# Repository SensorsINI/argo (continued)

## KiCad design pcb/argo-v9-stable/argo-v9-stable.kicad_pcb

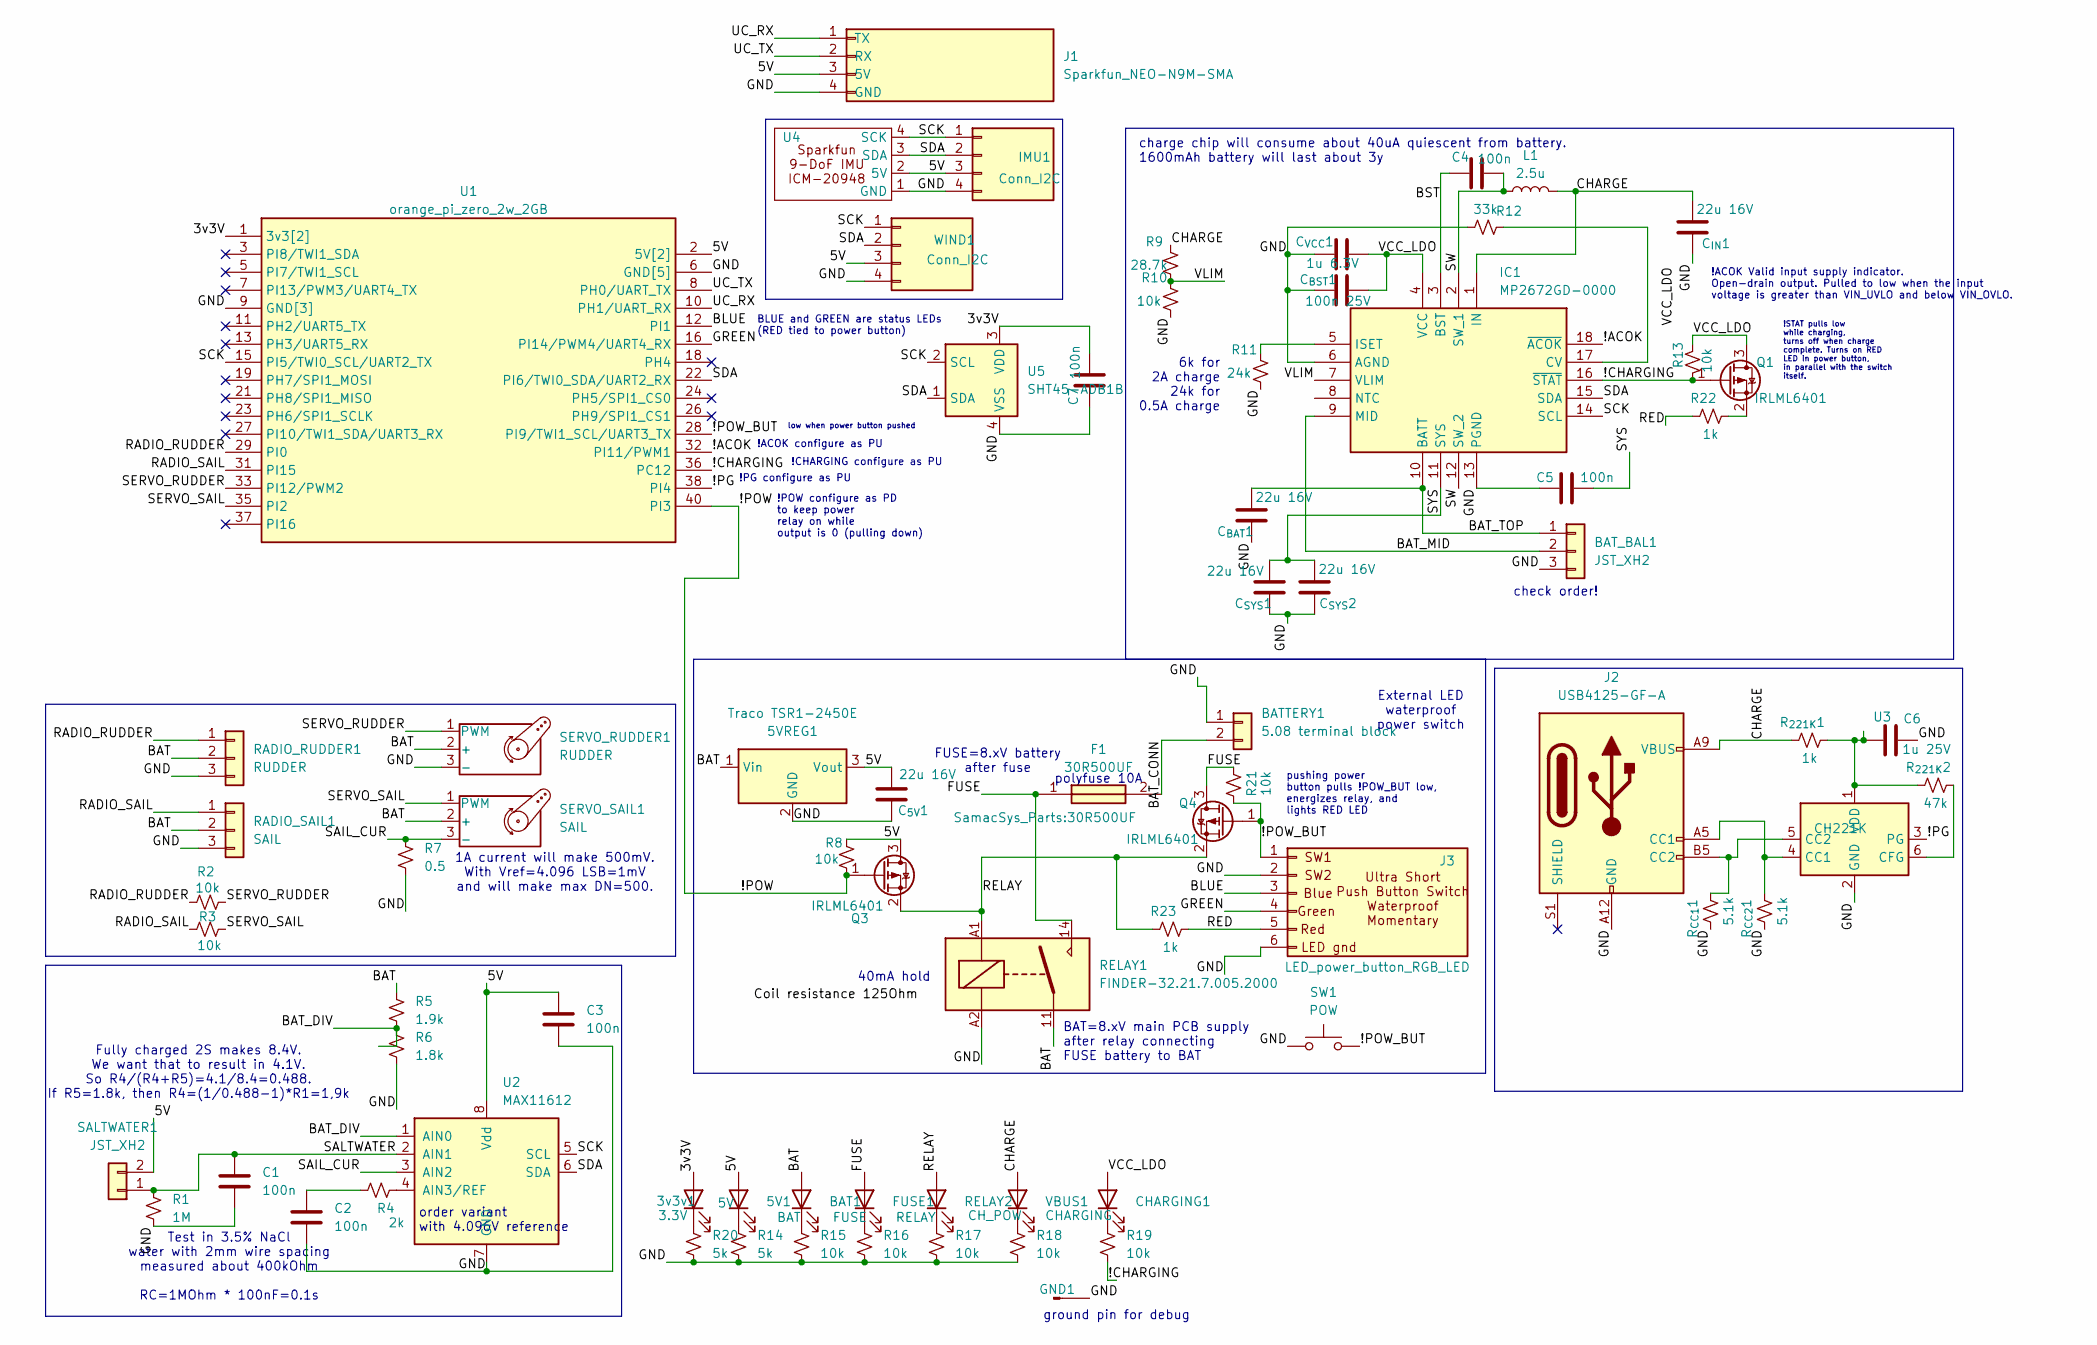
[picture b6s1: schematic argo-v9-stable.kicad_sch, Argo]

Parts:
3v3v1: 3.3V; LED_0603_1608Metric_Pad1.05x0.95mm_HandSolder
5V1: 5V; LED_0603_1608Metric_Pad1.05x0.95mm_HandSolder
5VREG1: Traco TSR1-2450E; Converter_DCDC_TRACO_TSR1-xxxxE_THT
BAT1: BAT; LED_0603_1608Metric_Pad1.05x0.95mm_HandSolder
BATTERY1: 5.08 terminal block; TerminalBlock_Phoenix_MKDS-1,5-2-5.08_1x02_P5.08mm_Horizont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
BAT_BAL1: JST_XH2; JST_XH_S3B-XH-A-1_1x03_P2.50mm_Horizontal
C1, C2, C3, C4, C5, C7: 100n; C_0603_1608Metric_Pad1.08x0.95mm_HandSolder
C6: 1u 25V; C_0603_1608Metric_Pad1.08x0.95mm_HandSolder
CHARGING1: CHARGING; LED_0603_1608Metric_Pad1.05x0.95mm_HandSolder
C_{5V}1: 22u 16V; C_1210_3225Metric_Pad1.33x2.70mm_HandSolder
C_{BAT}1: 22u 16V; C_1210_3225Metric_Pad1.33x2.70mm_HandSolder
C_{BST}1: 100n 25V; C_0603_1608Metric_Pad1.08x0.95mm_HandSolder
C_{IN}1: 22u 16V; C_1210_3225Metric_Pad1.33x2.70mm_HandSolder
C_{SYS}1, C_{SYS}2: 22u 16V; C_1210_3225Metric_Pad1.33x2.70mm_HandSolder
C_{VCC}1: 1u 6.3V; C_0603_1608Metric_Pad1.08x0.95mm_HandSolder
F1: 30R500UF; Mouser Part Number 576-30R500UF
FUSE1: FUSE; LED_0603_1608Metric_Pad1.05x0.95mm_HandSolder
GND1: Conn_01x01_Pin; Pin_D1.0mm_L10.0mm_LooseFit
IC1: MP2672GD-0000; QFN40P200X300X100-18N-D-handsolder; Manufacturer_Part_Number MP2672GD-0000
IMU1: Conn_I2C; JST_XH_B4B-XH-AM_1x04_P2.50mm_Vertical
J1: Sparkfun_NEO-N9M-SMA; Sparkfun_NEO-M9N-SMA-scaled
J2: USB4125-GF-A; USB_C_Receptacle_GCT_USB4125-xx-x-0190_6P_TopMnt_Horizontal
J3: LED_power_button_RGB_LED; JST_XH_B6B-XH-AM_1x06_P2.50mm_Vertical
L1: 2.5u; L_1210_3225Metric_Pad1.42x2.65mm_HandSolder
Q1, Q3, Q4: IRLML6401; SOT-23
R1: 1M; R_0603_1608Metric_Pad0.98x0.95mm_HandSolder
R2, R3, R8, R10, R13, R15, R16, R17, R18, R19, R21: 10k; R_0603_1608Metric_Pad0.98x0.95mm_HandSolder
R4: 2k; R_0603_1608Metric_Pad0.98x0.95mm_HandSolder
R5: 1.9k; R_0603_1608Metric_Pad0.98x0.95mm_HandSolder
R6: 1.8k; R_0603_1608Metric_Pad0.98x0.95mm_HandSolder
R7: 0.5; R_0603_1608Metric_Pad0.98x0.95mm_HandSolder
R9: 28.7k; R_0603_1608Metric_Pad0.98x0.95mm_HandSolder
R11: 24k; R_0603_1608Metric_Pad0.98x0.95mm_HandSolder
R12: 33k; R_0603_1608Metric_Pad0.98x0.95mm_HandSolder
R14, R20: 5k; R_0603_1608Metric_Pad0.98x0.95mm_HandSolder
R22, R23: 1k; R_0603_1608Metric_Pad0.98x0.95mm_HandSolder
RADIO_RUDDER1: RUDDER; PinHeader_1x03_P2.54mm_Vertical
RADIO_SAIL1: SAIL; PinHeader_1x03_P2.54mm_Vertical
RELAY1: FINDER-32.21.7.005.2000; Relay_SPST_Finder_32.21-x300
RELAY2: RELAY; LED_0603_1608Metric_Pad1.05x0.95mm_HandSolder
R_{221K}1: 1k; R_0603_1608Metric_Pad0.98x0.95mm_HandSolder
R_{221K}2: 47k; R_0603_1608Metric_Pad0.98x0.95mm_HandSolder
R_{CC1}1, R_{CC2}1: 5.1k; R_0603_1608Metric_Pad0.98x0.95mm_HandSolder
SALTWATER1: JST_XH2; JST_XH_S2B-XH-A_1x02_P2.50mm_Horizontal
SERVO_RUDDER1: RUDDER; PinHeader_1x03_P2.54mm_Vertical
SERVO_SAIL1: SAIL; PinHeader_1x03_P2.54mm_Vertical
SW1: POW; SW_Tactile_SPST_NO_Straight_CK_PTS636Sx25SMTRLFS
U1: orange_pi_zero_2w_2GB; orange_pi_zero_2w
U2: MAX11612; MSOP-8_3x3mm_P0.65mm
U3: CH221K; TSOT-23-6_HandSoldering
U4: Sparkfun_IMU_ICM-20948
U5: SHT45-ADB1B; Sensirion_DFN-4_1.5x1.5mm_P0.8mm_SHT4x_NoCentralPad
VBUS1: CH_POW; LED_0603_1608Metric_Pad1.05x0.95mm_HandSolder
WIND1: Conn_I2C; JST_XH_B4B-XH-AM_1x04_P2.50mm_Vertical

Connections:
/3v3V: 3v3v1.2 (A), C7.2, U1.1 (3v3[2]), U1.17 (3v3[2]), U5.3 (VDD)
/5V: 5V1.2 (A), 5VREG1.3 (Vout), C3.1, C_{5V}1.2, IMU1.3 (5V), J1.3 (5V), Q3.3 (D), R8.2, SALTWATER1.2, U1.2 (5V[2]), U1.4 (5V[2]), U2.8 (Vdd), U4.2 (5V), WIND1.3 (5V)
/!ACOK: IC1.18 (~ACOK), U1.32 (PI11/PWM1)
/!CHARGING: IC1.16 (~STAT), Q1.1 (G), R13.2, R19.2, U1.36 (PC12)
/!PG: U1.38 (PI4), U3.3 (PG)
/!POW: Q3.1 (G), R8.1, U1.40 (PI3)
/!POW_BUT: J3.1, Q4.1 (G), R21.2, SW1.2, U1.28 (PI9/TWI1_SCL/UART3_TX)
/BAT: 5VREG1.1 (Vin), BAT1.2 (A), R5.1, RADIO_RUDDER1.2, RADIO_SAIL1.2, RELAY1.11, SERVO_RUDDER1.2 (+), SERVO_SAIL1.2 (+)
/BAT_CONN: BATTERY1.2, F1.2
/BAT_DIV: R5.2, R6.1, U2.1 (AIN0)
/BAT_MID: BAT_BAL1.2, IC1.9 (MID)
/BAT_TOP: BAT_BAL1.1, C_{BAT}1.2, IC1.10 (BATT)
/BLUE: J3.3, U1.12 (PI1)
/BST: C4.1, IC1.3 (BST)
/CHARGE: C_{IN}1.2, IC1.1 (IN), J2.A9 (VBUS), J2.B9 (VBUS), L1.2, R9.1, R_{221K}1.1, VBUS1.2 (A)
/FUSE: F1.1, FUSE1.2 (A), Q4.3 (D), R21.1, RELAY1.14
/GND: 5VREG1.2 (GND), BATTERY1.1, BAT_BAL1.3, C1.2, C2.2, C3.2, C5.1, C6.2, C7.1, C_{5V}1.1, C_{BAT}1.1, C_{BST}1.1, C_{IN}1.1, C_{SYS}1.1, C_{SYS}2.1, C_{VCC}1.1, GND1.1, IC1.6 (AGND), IC1.13 (PGND), IMU1.4 (GND), J1.4 (GND), J2.A12 (GND), J2.B12 (GND), J3.2, J3.6, R1.2, R6.2, R7.2, R10.2, R11.2, R12.2, R14.2, R15.2, R16.2, R17.2, R18.2, R20.2, RADIO_RUDDER1.3, RADIO_SAIL1.3, RELAY1.A2, R_{CC1}1.1, R_{CC2}1.1, SERVO_RUDDER1.3 (-), SW1.1, U1.6 (GND[5]), U1.9 (GND[3]), U1.14 (GND[5]), U1.20 (GND[5]), U1.25 (GND[3]), U1.30 (GND[5]), U1.34 (GND[5]), U1.39 (GND[3]), U2.7 (GND), U3.2 (GND), U4.1 (GND), U5.4 (VSS), WIND1.4 (GND)
/GREEN: J3.4, U1.16 (PI14/PWM4/UART4_RX)
/RADIO_RUDDER: R2.1, RADIO_RUDDER1.1, U1.29 (PI0)
/RADIO_SAIL: R3.1, RADIO_SAIL1.1, U1.31 (PI15)
/RED: J3.5, R22.1, R23.2
/RELAY: Q3.2 (S), Q4.2 (S), R23.1, RELAY1.A1, RELAY2.2 (A)
/SAIL_CUR: R7.1, SERVO_SAIL1.3 (-), U2.3 (AIN2)
/SALTWATER: C1.1, R1.1, SALTWATER1.1, U2.2 (AIN1)
/SCK: IC1.14 (SCL), IMU1.1 (SCLK), U1.15 (PI5/TWI0_SCL/UART2_TX), U2.5 (SCL), U4.4 (SCK), U5.2 (SCL), WIND1.1 (SCLK)
/SDA: IC1.15 (SDA), IMU1.2 (SDA), U1.22 (PI6/TWI0_SDA/UART2_RX), U2.6 (SDA), U4.3 (SDA), U5.1 (SDA), WIND1.2 (SDA)
/SERVO_RUDDER: R2.2, SERVO_RUDDER1.1 (PWM), U1.33 (PI12/PWM2)
/SERVO_SAIL: R3.2, SERVO_SAIL1.1 (PWM), U1.35 (PI2)
/SW: C4.2, IC1.2 (SW_1), IC1.12 (SW_2), L1.1
/SYS: C5.2, C_{SYS}1.2, C_{SYS}2.2, IC1.11 (SYS)
/UC_RX: J1.1 (TX), U1.10 (PH1/UART_RX)
/UC_TX: J1.2 (RX), U1.8 (PH0/UART_TX)
/VCC_LDO: CHARGING1.2 (A), C_{BST}1.2, C_{VCC}1.2, IC1.4 (VCC), Q1.3 (D), R13.1
/VLIM: IC1.7 (VLIM), R9.2, R10.1
unnamed: 3v3v1.1 (K), R20.1
unnamed: 5V1.1 (K), R14.1
unnamed: BAT1.1 (K), R15.1
unnamed: C2.1, R4.2
unnamed: CHARGING1.1 (K), R19.1
unnamed: FUSE1.1 (K), R16.1
unnamed: IC1.17 (CV), R12.1
unnamed: IC1.5 (ISET), R11.1
unnamed: J2.A5 (CC1), R_{CC2}1.2, U3.4 (CC1)
unnamed: J2.B5 (CC2), R_{CC1}1.2, U3.5 (CC2)
unnamed: Q1.2 (S), R22.2
unnamed: R17.1, RELAY2.1 (K)
unnamed: R4.1, U2.4 (AIN3/REF)
unnamed: R_{221K}2.2, U3.6 (CFG)
unnamed: C6.1, R_{221K}1.2, R_{221K}2.1, U3.1 (VDD)
unnamed: R18.1, VBUS1.1 (K)

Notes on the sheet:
ground pin for debug
!PG configure as PU
!ACOK configure as PU
FUSE=8.xV battery after fuse
6k for 2A charge 24k for 0.5A charge
pushing power button pulls !POW_BUT low, energizes relay, and lights RED LED
1A current will make 500mV. With Vref=4.096 LSB=1mV and will make max DN=500.
Fully charged 2S makes 8.4V. We want that to result in 4.1V. So R4/(R4+R5)=4.1/8.4=0.488. If R5=1.8k, then R4=(1/0.488-1)*R1=1,9k
BLUE and GREEN are status LEDs (RED tied to power button)
check order!
!ACOK Valid input supply indicator. Open-drain output. Pulled to low when the input voltage is greater than VIN_UVLO and below VIN_OVLO.
!CHARGING configure as PU
BAT=8.xV main PCB supply after relay connecting FUSE battery to BAT
40mA hold
!POW configure as PD to keep power relay on while output is 0 (pulling down)
low when power button pushed
External LED waterproof power switch
!STAT pulls low while charging, turns off when charge complete. Turns on RED LED in power button, in parallel with the switch itself.
charge chip will consume about 40uA quiescent from battery. 1600mAh battery will last about 3y
Test in 3.5% NaCl water with 2mm wire spacing measured about 400kOhm RC=1MOhm * 100nF=0.1s
polyfuse 10A
order variant with 4.096V reference

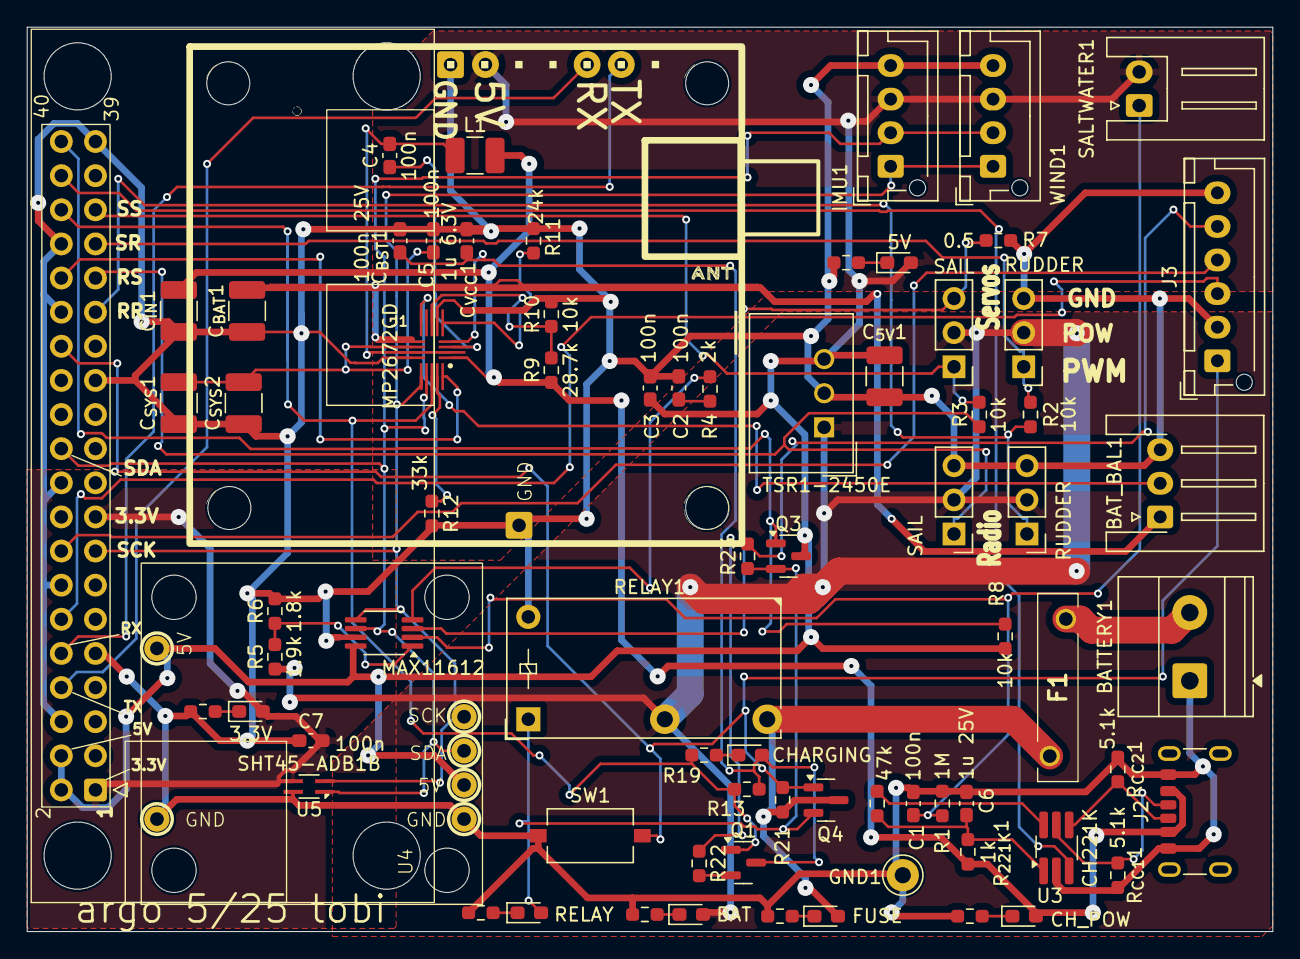
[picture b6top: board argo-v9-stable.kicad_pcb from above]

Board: 2 copper layers, 92.7 x 67.3 mm, 75 parts (0 on the bottom side), 50 nets.

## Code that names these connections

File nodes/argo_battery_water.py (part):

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# 
# MP2672 Charger Configuration:
# - MP2672_HOST_CONTROL constant controls operating mode:
#   * False (default): Standalone mode - uses GPIO only for charging and AC power status
#   * True: Host control mode - uses I2C registers (primary) and GPIO (fallback)
# 
# MP2672 Charger I2C Support (when MP2672_HOST_CONTROL = True):
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# - battery_voltage (V), saltwater_voltage (V), sail_current (A), pcb_temperature (C), relative_humidity (%)
# - battery_remaining_pct (%) using per‑cell LiPo formula: soc% = S − S/(1 + (v/V0)^A)^B
# Publishes (Bool):
# - charging_status (true=charging, false=not charging) - from MP2672 I2C or GPIO
# - ac_power_present (true=AC/USB power present, false=not present) - from MP2672 I2C or GPIO
# Alerts (Bool):
# - battery_low_alert (hysteresis 50 mV around battery_low_threshold_v; warning on low, info on recover)
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# - soc_S (123.0), soc_V0 (3.7), soc_A (80.0), soc_B (0.165)
# Hardware:
# - I2C Bus: Exclusively uses I2C bus 0 (Orange Pi Zero 2W default I2C interface)
# - I2C Pins: SDA=PI6 (twi0-sda), SCL=PI5 (twi0-sck) - configured via pi-i2c0 overlay
# - MAX11612 ADC at I2C address 0x34, SHT45 sensor at I2C address 0x44
# - MP2672 charger at I2C address 0x4B (only accessible when USB power present and MP2672_HOST_CONTROL = True)
# - GPIO Pins: PC12 (pin 36, line 76) !CHARGING, PH9 (pin 26, line 233) !ACOK from MP2672GD; PI4 (pin 38, line 260) !PG from CH221K USB-C voltage controller Pin 3 (open-drain, active low, requires pull-up)
#   - !PG indicates successful USB Power Delivery (PD) negotiation - LOW = PD successful, HIGH = no PD (standard USB) or failed
#   - Note: With standard USB cables (non-PD), this will be HIGH, not an indication of power failure
# - HOST_CTL: GPIO 229 (pin 24) tied high via hardware pullup resistor for host control mode
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# Note: REG 05H is OTP-only and not accessible to customers

# GPIO configuration for MP2672GD charger status
CHARGING_GPIO_LINE = 76   # PC12 (pin 36) - !CHARGING from MP2672GD
ACOK_GPIO_LINE = 233      # PH9 (pin 26) - !ACOK from MP2672GD
PG_GPIO_LINE = 260        # PI4 (pin 38) - !PG from CH221K USB-C voltage controller Pin 3 (open-drain output, active low, REQUIRES external pull-up)
                         # Indicates successful USB Power Delivery (PD) negotiation: LOW = PD successful, HIGH = no PD (standard USB) or failed
                         # Note: With standard USB cables (non-PD), this will be HIGH - not an indication of power failure
HOST_CTL_GPIO_LINE = 229  # PH5/SPI1_CS0 (pin 24) - HOST_CTL to MP2672GD (not used, MPC2672GD reads CV pin on power-on only)

# Sample rate configuration - dual timers for different sensor requirements
SAIL_CURRENT_RATE_HZ = 5.0  # Hz for sail current (control critical)
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            'humidity_alert': False,
            'charging_status': None,
            'ac_power_present': None,
            'usb_pd_negotiated': False,  # CH221K !PG GPIO (PI4, pin 38): True = USB PD negotiation successful, False = no PD (standard USB) or failed
            'charging_fault_detected': False,  # GPIO-based fault detection: True if 1-2 Hz blinking pattern detected
            'charging_fault_frequency': None,  # Frequency (Hz) of blinking if fault detected
            'time_to_full_hours': None,
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            try:
                # Initialize GPIO chip
                self.gpio_chip = gpiod.Chip("/dev/gpiochip0")
                # Request charging status GPIO line (PC12, line 76)
                # MP2672 pulls this line LOW when charging, so we need pullup to detect HIGH when not charging
                self.charging_gpio_line = self.gpio_chip.get_line(CHARGING_GPIO_LINE)
                self.charging_gpio_line.request(
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                    type=gpiod.LINE_REQ_DIR_IN,
                    flags=gpiod.LINE_REQ_FLAG_BIAS_PULL_UP
                )
                # Request AC power status GPIO line (PH9, line 233)
                # MP2672 pulls this line LOW when USB power is present, so we need pullup to detect HIGH when not powered
                self.acok_gpio_line = self.gpio_chip.get_line(ACOK_GPIO_LINE)
                self.acok_gpio_line.request(
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                    type=gpiod.LINE_REQ_DIR_IN,
                    flags=gpiod.LINE_REQ_FLAG_BIAS_PULL_UP
                )
                # Request USB PD negotiation status GPIO line (PI4, line 260, pin 38)
                # CH221K PG pin (Pin 3) is open-drain output, active low - REQUIRES external pull-up (3.3V) to work correctly
                # Indicates successful USB Power Delivery (PD) negotiation of requested voltage (e.g., 5V, 9V, 12V, 15V, 20V)
                # Active low: CH221K pulls LOW when PD negotiation successful, leaves floating (HIGH via pull-up) when no PD or failed
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        self.get_logger().info('=== BATTERY_WATER_NODE SHUTDOWN START ===')
        self.get_logger().info(f"Received signal {signum}, saving slopes and shutting down...")
        
        # Set shutdown flags to stop both timer callbacks and main spin loop
        self._shutdown_requested = True
        self.shutdown_requested = True  # Flag checked by spin_once() loop
        
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            if battery_data.get('charging_anomaly') is True:
                active_alerts.append('⚠️ CHARGER POWER FAULT')
            
            # GPIO-based charging fault detection (standalone mode - no I2C access)
            # MP2672 datasheet: 1Hz blinking on STAT pin indicates fault conditions
            if battery_data.get('charging_fault_detected') is True:
                freq = battery_data.get('charging_fault_frequency')
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        # Bits 5-4 (CHG_STAT [1:0]): 2-bit charging status
        #   00 = Not charge
        #   01 = Pre-charge
        #   10 = Constant-current/constant-voltage charge (charging)
        #   11 = Charge done
        #
        # Bit 3 (PPM_STAT): Power Path Management status
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                self.get_logger().debug("MP2672 I2C communication error (normal when USB power not present)")
            return False

    # ---------- Charging status reading (MP2672 I2C with GPIO fallback) ----------
    def _read_charging_status(self):
        """
        Read charging status from MP2672 I2C register (primary) or GPIO (fallback).
        
        Priority:
        1. MP2672 I2C register 0x03 (if available and MP2672_HOST_CONTROL = True)
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        if charging_status_recent and not ac_power_present:
            if (current_time - self._last_charging_conflict_log_time) >= self._charging_conflict_log_interval:
                self.get_logger().warning(
                    "Charging GPIO asserted but AC power is absent; suppressing charging status (check charger hardware)."
                )
                self._last_charging_conflict_log_time = current_time
            # Age out the stale charging timestamp so it clears immediately
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            ac_power_raw = False
            if self.acok_gpio_line is not None:
                acok_gpio_value = self.acok_gpio_line.get_value()
                ac_power_raw = not acok_gpio_value  # Invert: !ACOK=0 means AC power present=True
                if ac_power_raw:
                    self._last_ac_power_true_time = current_time
            
            # Read !CHARGING GPIO (PC12, line 76) - invert logic for charging status
            # Note: Code uses !CHARGING (PC12) for transition tracking; MP2672 datasheet describes 1Hz blink on STAT.
            # When no charger is present, !CHARGING may toggle (floating/different IC state) and must not be reported as fault.
            if self.charging_gpio_line is not None:
                charging_gpio_value = self.charging_gpio_line.get_value()
                charging_raw = not charging_gpio_value  # Invert: !CHARGING=0 means charging=True
                
                # Track GPIO transitions for fault detection (1-2 Hz blinking pattern)
                # MP2672 datasheet: 1Hz blinking on STAT pin indicates fault conditions
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                if charging_raw:
                    self._last_charging_true_time = current_time
            
            # Read !PG GPIO (PI4, line 260, pin 38) from CH221K USB-C voltage controller
            # CH221K PG pin (Pin 3) indicates successful USB Power Delivery (PD) negotiation
            # Active low: Hardware LOW = PD negotiation successful, Hardware HIGH (via pull-up) = no PD (standard USB) or failed
            # Note: With standard USB cables (non-PD), this will be HIGH - not an indication of power failure
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            battery_remaining_pct = self._latest_battery_remaining_pct
        self._latest_battery_remaining_pct = battery_remaining_pct

        # Check MP2672 availability and read charging status (I2C primary if host control enabled, GPIO fallback)
        if MP2672_HOST_CONTROL:
            self._check_mp2672_availability()
            # Read MP2672 CHG timer configuration if available
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                    chg_stat_names = {
                        0b00: 'Not charge',
                        0b01: 'Pre-charge',
                        0b10: 'Constant-current/constant-voltage charge',
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
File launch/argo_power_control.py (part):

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#   by GPIO pin state reversion on system halt.
#
# HARDWARE CONFIGURATION:
#   - PI3 (Pin 40): !POW - Open drain output to control power relay
#   - PI9 (Pin 28): !POW_BUT - Input from power button (external pullup required)
#   - PH4 (Pin 18): Green LED in power button (system running indicator)
#   - PI1 (Pin 12): Blue LED in power button (status/warning indicator)
#   - Red LED: Directly connected to power button (not GPIO controlled)
#
# POWER CIRCUIT DESIGN:
#   The system uses two PFETs to control the power relay:
#   1. Direct PFET: Connected to power button for immediate power-on
#   2. GPIO PFET: Connected to !POW pin for software-controlled power management
#   
#   When !POW is pulled low (open drain), the relay is energized, providing power.
#   When !POW goes high, the relay is de-energized, cutting power.
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#   2. Wait 5 seconds for users to see notification
#   3. Start alternating short-long LED pattern (shutdown indicator)
#   4. Execute 'sudo shutdown -h now' for graceful shutdown
#   5. GPIO pins will automatically revert to input state on halt, de-energizing relay
#
# USAGE:
#   ./argo_power_control.py [--help] [--test-mode] [--threshold SECONDS]
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
# Shutdown Sequence Timing
SHUTDOWN_NOTIFICATION_DELAY_S = 5       # Wait time for users to see notification (seconds)
SHUTDOWN_RELAY_DELAY_S = 10              # Delay before de-energizing relay (seconds)
SHUTDOWN_CACHE_FLUSH_TIMEOUT_S = 10     # SD card cache flush timeout (seconds)

# Notification Timeouts
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NOTIFICATION_EXPIRE_TIME_MS = 5000      # Notification expire time (milliseconds)

# Main Loop Timing
MAIN_LOOP_SLEEP_S = 1                   # Main control loop sleep interval (seconds)

# Configure logging
def setup_logging():
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        self.GPIO_CHIP = '/dev/gpiochip0'
        
        # Correct GPIO Line offsets from gpio readall
        self.POWER_RELAY_LINE = 259    # PI3 (Pin 40) - !POW
        self.POWER_BUTTON_LINE = 265   # PI9 (Pin 28) - !POW_BUT  
        self.GREEN_LED_LINE = 228      # PH4 (Pin 18) - Green LED
        self.BLUE_LED_LINE = 257       # PI1 (Pin 12) - Blue LED
        
        # Button press threshold (seconds)
        self.SHUTDOWN_THRESHOLD = threshold
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            subprocess.run(['shutdown', '-h', 'now'], check=True)
            logger.info("Shutdown command executed successfully")
            # Don't set self.running = False here - let the system shutdown
            # GPIO pins will automatically revert to input state on halt, de-energizing relay


    def run(self):
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  by GPIO pin state reversion on system halt.

HARDWARE CONFIGURATION:
  - PI3 (Pin 40): !POW - Open drain output to control power relay
  - PI9 (Pin 28): !POW_BUT - Input from power button (external pullup required)
  - PH4 (Pin 18): Green LED in power button (system running indicator)
  - PI1 (Pin 12): Blue LED in power button (status/warning indicator)
  - Red LED: Directly connected to power button (not GPIO controlled)

POWER BUTTON BEHAVIOR:
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SAFETY FEATURES:
  - Open drain configuration prevents damage from multiple control sources
  - Graceful shutdown ensures proper system shutdown before cutting power
  - GPIO pins automatically revert to input state on halt, de-energizing relay
  - External pullup resistor requirement prevents floating inputs
  - GPIO group membership requirement for controlled GPIO access
"""
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
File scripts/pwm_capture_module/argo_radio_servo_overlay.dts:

// SPDX-License-Identifier: GPL-2.0
// DTS for Argo Radio Servo Module Overlay on Orange Pi Zero 2W (Allwinner H618)
// This overlay configures EINT input pins and explicitly defines PWM channels 2 and 4
// for control via the kernel's generic PWM API (pwm_get).

#include <dt-bindings/interrupt-controller/irq.h>
#include <dt-bindings/interrupt-controller/arm-gic.h>
#include <dt-bindings/gpio/gpio.h> // For GPIO_ACTIVE_HIGH/LOW, etc.


/dts-v1/;
/plugin/;

/ {
    compatible = "xunlong,orangepi-zero2w", "allwinner,sun50i-h618";

    // --- Fragment 0: Add the argo platform device to the root node ---
    fragment@0 {
        target-path = "/";
        __overlay__ {
            // Node for our kernel module to claim GPIOs (using compatible for lookup)
            // This node now also controls the pin multiplexing for the EINT pins.
            argo_radio_servo_gpios: argo_radio_servo_gpios {
                compatible = "argo,radio-servo-gpio";
                radio_rudder-gpios = <&pio 8 11 GPIO_ACTIVE_HIGH>; // PI11
                radio_sail-gpios = <&pio 8 13 GPIO_ACTIVE_HIGH>;   // PI13
                pwms = <&pwm 2 20000 0>, <&pwm 4 20000 0>; // PWM controller channels 2 and 4
                pwm-names = "pwm2", "pwm4"; // Labels for devm_pwm_get
                status = "okay";
            };
        };
    };

    // --- Fragment 1: Explicitly disable the Ethernet GMAC controller itself ---
    frag_emac_disable: fragment@1 {
        target = <&emac1>;
        __overlay__ {
            status = "disabled";
        };
    };

    // Fragment 2 removed - GPIO pins don't need explicit pinctrl configuration
    // when used directly as GPIOs via the gpiod subsystem

    // following commented out because we use armbian pwm output overlay instead
    // --- Fragment 3: Define PWM Output Pinmuxing Groups for PI12 and PI14 ---
    /* fragment@3 {
        target = <&pio>; // Target the main pinctrl node
        __overlay__ {
            // PI12 (PWM2_SERVO_RUDDER) - Output
            pi12_pwm2_out_group: pi12_pwm2_out_group {
                pins = "PI12";
                function = "pwm2"; // As per manual's PI12_SELECT (101:PWM2)
            };

            // PI14 (PWM4_SERVO_SAIL) - Output
            pi14_pwm4_out_group: pi14_pwm4_out_group {
                pins = "PI14";
                function = "pwm4"; // As per manual's PI14_SELECT (101:PWM4)
            };
        };
    };
    */
};

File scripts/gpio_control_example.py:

#!/usr/bin/env python3
#
# gpio_control_example.py
#
# Description:
#   A script to demonstrate GPIO control on an Orange Pi Zero 2W using the
#   libgpiod library. This is the modern, recommended method for GPIO
#   manipulation on Linux systems.
#
# Prerequisites:
#   - The libgpiod library and its Python bindings must be installed.
#     On Debian-based systems (like Armbian for Orange Pi), you can install it with:
#     sudo apt-get update
#     sudo apt-get install gpiod python3-gpiod
#
# Pin Numbering:
#   libgpiod identifies GPIOs by their chip and line offset, not by the physical
#   pin number on the header or the SoC name (e.g., "PA6").
#
#   To find the correct chip and line offset for a physical pin, use the
#   `gpioinfo` command in your terminal.
#
#   Example for Orange Pi Zero 2W (Allwinner H616):
#   $ gpioinfo
#   gpiochip0 - 256 lines:
#       ...
#       line   6:      "PA6"       unused   input  active-high
#       ...
#       line 226:      "PH2"       unused   input  active-high
#       line 227:      "PH3"       unused   input  active-high
#       ...
#
#   From this output, we can see:
#   - The GPIO chip is 'gpiochip0'.
#   - The GPIO pin named "PA6" (physical pin 7) corresponds to line offset 6.
#   - The GPIO pin named "PH2" (physical pin 11) corresponds to line offset 226.
#   - The GPIO pin named "PH3" (physical pin 13) corresponds to line offset 227.

import gpiod
import time
import sys

# --- Configuration ---
# Use `gpioinfo` to find the correct chip for your board.
# For Orange Pi Zero 2W, it's typically 'gpiochip0'.
GPIO_CHIP = 'gpiochip0'

# Define the line offsets for the pins you want to control.
# See "Pin Numbering" section above for how to find these.
OUTPUT_PIN_OFFSET = 6      # Physical Pin 7 (PA6)
INPUT_PULL_UP_PIN_OFFSET = 226 # Physical Pin 11 (PH2)
INPUT_PULL_DOWN_PIN_OFFSET = 227 # Physical Pin 13 (PH3)

def main():
    """
    Main function to demonstrate GPIO control.
    """
    # Get a handle to the GPIO chip
    try:
        chip = gpiod.Chip(GPIO_CHIP)
    except (FileNotFoundError, PermissionError) as e:
        print(f"Error: Could not open GPIO chip '{GPIO_CHIP}': {e}", file=sys.stderr)
        print("Please check the chip name with 'gpioinfo' and run with 'sudo' or as a user in the 'gpio' group.", file=sys.stderr)
        sys.exit(1)

    # --- 1. Configure a pin as an OUTPUT ---
    output_line = chip.get_line(OUTPUT_PIN_OFFSET)
    output_line.request(
        consumer="gpio_control_example.py",
        type=gpiod.LINE_REQ_DIR_OUT,
        default_vals=[0] # Start with the pin low
    )
    print(f"Line {OUTPUT_PIN_OFFSET} configured as OUTPUT.")

    # --- 2. Configure a pin as an INPUT with PULL-UP ---
    input_pull_up_line = chip.get_line(INPUT_PULL_UP_PIN_OFFSET)
    input_pull_up_line.request(
        consumer="gpio_control_example.py",
        type=gpiod.LINE_REQ_DIR_IN,
        flags=gpiod.LINE_REQ_FLAG_BIAS_PULL_UP
    )
    print(f"Line {INPUT_PULL_UP_PIN_OFFSET} configured as INPUT with PULL-UP.")

    # --- 3. Configure a pin as an INPUT with PULL-DOWN ---
    # Note: Not all SoCs/pins support pull-down. If this fails, your hardware
    # may not support it on this specific pin.
    input_pull_down_line = chip.get_line(INPUT_PULL_DOWN_PIN_OFFSET)
    try:
        input_pull_down_line.request(
            consumer="gpio_control_example.py",
            type=gpiod.LINE_REQ_DIR_IN,
            flags=gpiod.LINE_REQ_FLAG_BIAS_PULL_DOWN
        )
        print(f"Line {INPUT_PULL_DOWN_PIN_OFFSET} configured as INPUT with PULL-DOWN.")
    except OSError as e:
        print(f"Warning: Could not set PULL-DOWN on line {INPUT_PULL_DOWN_PIN_OFFSET}: {e}", file=sys.stderr)
        print("The pin may not support pull-down resistors. Continuing without it.", file=sys.stderr)
        input_pull_down_line = None

    print("\n--- Starting GPIO Demo ---")
    print("Blinking output pin and reading input pins for 10 seconds.")
    print("Press Ctrl+C to exit.")

    try:
        for i in range(20):
            # Toggle the output pin
            output_line.set_value(i % 2)

            # Read the input pins
            pull_up_val = input_pull_up_line.get_value()
            pull_down_val_str = "N/A"
            if input_pull_down_line:
                pull_down_val = input_pull_down_line.get_value()
                pull_down_val_str = "HIGH" if pull_down_val == 1 else "LOW"

            print(
                f"Output (line {OUTPUT_PIN_OFFSET}): {'HIGH' if (i % 2) == 1 else 'LOW'} | "
                f"Input PU (line {INPUT_PULL_UP_PIN_OFFSET}): {'HIGH' if pull_up_val == 1 else 'LOW'} | "
                f"Input PD (line {INPUT_PULL_DOWN_PIN_OFFSET}): {pull_down_val_str}"
            )
            time.sleep(0.5)
    except KeyboardInterrupt:
        print("\nExiting.")
    finally:
        print("Releasing GPIO lines...")
        chip.close()
        print("GPIO lines released. Done.")

if __name__ == "__main__":
    main()

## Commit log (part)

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2025-11-21 Add shutdown logging system to diagnose slow shutdowns
    - Add shutdown-logger.service: systemd service that runs early during
    shutdown to capture service stop times and timing information
    - Add shutdown-logger.sh script: logs active systemd jobs, service
    stop timeouts, and shutdown target information to persistent storage
    - Update argo_poweroff.shutdown hook: add persistent logging to
    /var/log.hdd/persistent/shutdown-hook-*.log files
2025-11-21 Fix shutdown logger timeout parsing
    - Use TimeoutStopUSec instead of TimeoutStopSec (systemd returns
    microseconds, not the formatted string)
    - Convert microseconds to seconds for human-readable output
    - Improve service filtering in long timeout section
    - Handle infinity timeout values properly
    This fixes the issue where timeouts showed as just 's' instead of
2025-11-22 Fix timeout command signal propagation
    - Skip os.setsid() when running under timeout command
    - timeout sends signals to its process group
    - os.setsid() creates new process group, breaking signal propagation
    - By skipping setsid() under timeout, signals reach the lifecycle manager
    - Improve signal handler with explicit flushing
    - Add finally block to ensure cleanup on loop exit
2025-11-22 screenshot of workiing crosser controller
2025-11-24 Add freeze-mac-address Makefile target
2025-11-24 Document automatic MAC address application during boot process
2025-11-24 Add human and crosser controllers to web dashboard and fix controller highlighting
    - Add human and crosser controller buttons to web dashboard API
    - Fix controller button highlighting for human and crosser controllers
    - Refactor controller highlighting logic to use mapping array (reduce duplication)
    - Arrange controller buttons in 2 columns side-by-side layout
    - Add I2C failure grace period (30s) during controller startup to prevent false RTH switches
    - Fix signal handler bug in lifecycle_manager when called from background thread
2025-11-27 increase saltwarter threshold with new sponge and 150kOhm resistor
2025-11-28 Reduce AC power detection latency for faster LED response
    - Change BATTERY_SAFETY_INTERVAL_S from 10s to 5s (faster topic publication)
    - Reduce _ac_power_window_s from 30s to 5s (faster AC power removal detection)
    - Update LED header comments to reflect green LED for charging status
    This reduces maximum LED transition latency from 30+ seconds to ~5-10 seconds
    when plugging/unplugging USB power. The time-windowed approach was causing
    30-second delays in detecting AC power removal.
2025-11-28 Add flash.xml detection and --no-fis fallback for GPS firmware flashing
    - Look for flash.xml in common locations (current dir, firmware/, u-center install)
    - Allow flash.xml as 4th argument
    - Use --no-fis 1 as fallback if flash.xml not found
    - flash.xml is required for proper firmware updates but --no-fis may work
2025-11-28 Add comprehensive README for SparkFun NEO-M9N firmware flashing
    - Document when to flash firmware (bootloader mode, updates, malfunctions)
    - Step-by-step flashing instructions
    - Post-flash configuration (NMEA enable, baud rate)
    - Troubleshooting guide for common issues
    - References to related scripts and documentation
2025-12-04 docs: Consolidate and expand battery power documentation
    - Rename README-plot-battery-water.md to README-battery-power.md
    - Expand documentation to include:
    * Battery monitoring node (SOC calculation, lifetime estimation, charging status)
    * Power control service (critical battery protection, LED patterns)
    * Health monitor integration
    * Data visualization (plotting functionality)
2025-12-04 docs: Document systemd graceful shutdown improvements and known issues
    Key Findings Documented:
    1. Root cause of force-kill issue: KillMode=mixed sends SIGKILL immediately to child processes
    2. Solution: KillMode=control-group allows all processes to receive SIGTERM
    3. Results: Clean shutdown in 1-2 seconds (was immediate SIGKILL or 10s timeout)
    New Sections:
    - Graceful Shutdown Implementation (Dec 2025) in Shutdown Sequence
2025-12-04 fix(alog): Fix foxglove channel filtering regex
    Changed from basic grep with escaped parens to extended regex (-E) with
    proper alternation syntax. This correctly filters out both 'Advertising'
    and 'Removing' channel messages from foxglove bridge.
    Before: Messages still appeared despite filter
    After: Clean logs without foxglove channel management spam
2025-12-04 Replace subprocess with direct ROS2 API in health monitor
    Problem: Health monitor used subprocess.run(['ros2', 'node', 'list']) which:
    - Could timeout (5s) causing intermittent failures
    - Was slow and inefficient
    - Created unnecessary process overhead
    - Could block during shutdown
    Solution: Use ros2node.api.get_node_names() direct API call
2025-12-06 made i2c readme
2025-12-16 fix(battery-water): Improve shutdown handling to prevent 80s delays
    - Add shutdown flag checks to I2C operations to prevent blocking during shutdown
    - Enhanced signal handler to cancel all timers immediately on SIGTERM
    - Initialize _i2c_failure_republish_timer to prevent AttributeError
    - Prevents I2C operations from blocking shutdown sequence
    Also includes:
    - Power control improvements for invalid battery reading handling
2025-12-23 argo pcb rev3 almost complete
2025-12-23 add kicad backup
2025-12-28 added missing symbol lib for relay
2025-12-28 close up photos
2025-12-28 make path absolute for robust import
2025-12-30 datasheet for SL connector family molex
2026-01-01 first steps to housing model. adjusted PCB layout slightly. fixed rules
2026-01-02 add digikey info, update i2c header for wind sensor, made digikey order
2026-01-13 added separators around rim of top part between pitot inputs
2026-01-16 wind sensor rev 1 housing 3d cad freecad
2026-01-17 add sensirion datasheet
2026-01-17 update view only
2026-01-17 update i2c cable
2026-01-17 one more try to show vid
2026-01-19 README updates to add links and recent news
2026-01-22 various fixes, most critically the SDP32 3d model was rotated 180deg. This is now fixed and the 3d design of top part of housing is fixed for the new SDP32 air inputs.
2026-01-23 fixed slot on mast step up to be 3mm wide, improved filleting. gave cable gland base a very slight -1 degree flare to hold in hull with snapping
2026-01-25 Clarify persistent logging setup and harden ramlog fix
    Document journald/ramlog and why Argo writes to /var/log.hdd/persistent. Update the orangepi-ramlog patch and fix script to exclude persistent/ in both sync directions to prevent zram fills.
2026-01-26 Fix I2C address conflict: LP5814 broadcast address conflicts with MAX11612
    - Document I2C address conflict between LP5814 (0x34 broadcast) and MAX11612 (0x34)
    - Add LP5814 alternatives documentation (KTD2027 recommended)
    - Update argo_battery_water.py with address conflict warnings
    - Update argo_mast_leds.py with new power control messages (untested)
    - Update argo_power_control.py to send LED control messages
    - Add I2C device documentation updates
2026-01-28 changed air temp to wind sensor temperature which is more accurate about what this temperature means (hotter than air temp from LED and SDP32 self-heating)
2026-02-01 Add battery storage rundown mode (astore): discharge to 7.6V then shut down
    - Power control: use 7.6V shutdown threshold when storage flag set; initiate
    halt at 7.6V (no AC bypass). Log 'Storage rundown' in voltage check.
    - Battery/water: expose battery_storage_rundown in /battery_status; append
    'Battery storage rundown to 7.6V' to status log; time-to-empty uses 7.6V
    target when storage mode active (else 6.0V).
    - Lifecycle manager: status/quick_status show storage mode and est. time to
2026-02-03 battery_status_genmon: show ??? when service unavailable or data invalid
    - Use ??? for service unavailable, errors, and timeout (no cached display)
    - Treat i2c_failure, stale_data, or invalid/NaN battery_voltage as invalid; show ??? and clear tooltip
    - Add _output_invalid() for I2C/stale/invalid voltage cases
    - Safe float formatting for tooltip (NaN/None) for saltwater, sail_current, temp, humidity
2026-02-03 plot-battery-water: add --slope to compute discharge slope (V/h) from CSV
    - compute_discharge_slope_vph(): linear regression on voltage vs time; optional
    exclude_drops_v to use longest segment (avoids power glitch / sharp drop)
    - --slope: print slope and exit; --slope-exclude-drops 0.3 (default) for robustness
2026-02-25 working version of complete boat model including sails, keel, rudder, hull (based on RG65 profile, not yet udpated for DF65), plus argo PCBs and other parts as step models
2026-03-15 align v4 pinout mapping and stabilize TWI2/PH4 integration
    Update nodes, scripts, and docs for the rev4 wiring changes by resolving the wind/mast TWI2 Linux bus dynamically, adding PH4 heartbeat overlay install into the default power-control flow, and docume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
    Made-with: Cursor
2026-03-15 move first startup beep to an early boot hook
    Install a dedicated sysinit one-shot boot beep service and remove the duplicate startup beep from argo_power_control so boot audio cues are early and non-redundant.
    Made-with: Cursor
2026-03-27 removed gps noise, made cross default controller
2026-03-28 BOM to build rev 4 PCB
2026-03-29 Fix video tag and update news section in README
    Updated video link format and added new news entries.
2026-04-03 add beep confirmation of shutdown or restart . Allow .1 e.g. beeps from CLI
2026-04-05 add command to remotely start anem.py for debugging it
2026-04-05 clean up pcb folder
2026-04-05 update rules for thermal and lora
2026-04-09 Host setup, dotfiles ROS, sim UX, keyboard UI, faster shell startup
    Makefile: Idempotent ROS apt source (avoid duplicate Signed-By), single
    apt-get update in install-deps, host-setup installs ros-base when missing,
    setup-venv skips interactive uv when .venv exists, install-python-deps uses
    uv pip when uv is available on hosts.
    README: Installation split for boat vs host; document host-setup, ROS LTS
    mapping, venv/uv, troubleshooting rclpy in current shell, and one-time
2026-04-09 fix PCB README
2026-04-15 crosser successfully crosses hotel dei pini sailing area with offshore breeze. Tacks upWind and jibes correctly. Tack duration extended.
2026-04-16 latest simulation visualization settings
2026-04-29 add hotel pool map
2026-04-29 add alias to restart everything
2026-04-30 Fix boat centering by applying GPS antenna offset.
    Publish odom->base_link at boat center (not gps_link) and use TF-derived pose for heading trail so Foxglove markers align consistently.
    Made-with: Cursor
2026-05-08 submodule sync with main, 300ms delay after reset of IMU
2026-05-08 add close to share geofenc, change it to be default, make human the default controller, remindder to refresh page for new map
2026-05-14 sailing area publisher map name improvmements
2026-05-16 increase reset timout to 10m, IMP:T: configure hot start before enabling NMEA sentences
2026-05-25 allow single node restart
2026-05-26 pcb and glands
2026-05-26 Fix power button GPIO shutdown race and stuck pressed state.
    Stop the interrupt monitor thread before releasing GPIO lines, guard
    against None line access during cleanup, and clear power_button_pressed
    when the release monitor exits abnormally.
2026-05-28 Raise GPS spike filter threshold to 3 m/s for transform publisher.
    The ~1 m/s DF65 hull-speed default rejected valid /fix updates during walking and testing, freezing boat position in /tf while heading still updated.
2026-06-03 latest v5 schematics and 3d design upated including hose coupleeer for pressure test
2026-06-11 Fix false MP2672 charging fault from stale STAT GPIO transitions.
    Clear the edge-history buffer on AC plug events and when the STAT pin has been steady, so floating pre-plug-in toggles no longer trigger persistent 2.22 Hz fault warnings during normal charging.
2026-06-13 next version of winch gland. Delete previous version
2026-06-21 turned off desktop notifications since we are rarely using monitor now
